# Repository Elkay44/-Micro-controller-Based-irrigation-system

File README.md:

This Arduino sketch is designed for an ESP8266 microcontroller and serves the purpose of monitoring and controlling various sensors, including a DHT11 temperature and humidity sensor, a soil moisture sensor, and a DS18B20 temperature sensor. It communicates with the Blynk platform to facilitate remote sensor data visualization and control. Here's a detailed description of the code:

Libraries and Includes: The code begins by including several libraries, such as Blynk, SimpleTimer, DHT, OneWire, and DallasTemperature. These libraries enable communication with sensors and the Blynk platform.

Variables and Constants: The code defines essential variables and constants, including Blynk authentication, Wi-Fi credentials (SSID and password), pin assignments, sensor thresholds, and relay control pin.

sendSensor() Function: This function is responsible for reading data from the DHT11 sensor, which measures humidity and temperature. It checks for data validity and sends these readings to the Blynk app for remote monitoring. Additionally, it attempts to read data from a soil sensor (though there is a variable 's' used in virtualWrite which is not defined in the code).

setup() Function: This function initializes the ESP8266 device, sets pin modes for various sensors and relay control, and begins serial communication for debugging and communication with the DHT sensor. It configures a timer to periodically call the sendSensor() function for sensor data updates and initializes the DallasTemperature library for the DS18B20 sensor.

sendTemps() Function: This function reads analog data from A0 and requests temperature data from the DS18B20 sensor. It then sends these temperature readings to the Blynk app for remote monitoring.

loop() Function: The main loop function continuously runs and performs the following tasks:

Handles Blynk communication and executes timed functions using the timer.
Calls the sendTemps() function to update temperature readings and sends them to Blynk.
Reads the state of the soil moisture sensor and takes actions based on its state:
If the soil is dry (sensorState is 1 and lastState is 0) and the limit is below 300, it sends a notification to water the plants and turns on the water valve.
If the soil is already wet (sensorState is 1 and lastState is 1), it indicates that the valve is not open.
Otherwise, it turns off the water valve and logs that the valve is closed.
The code effectively integrates multiple sensors, enabling remote monitoring of environmental conditions and plant watering control through the Blynk platform.

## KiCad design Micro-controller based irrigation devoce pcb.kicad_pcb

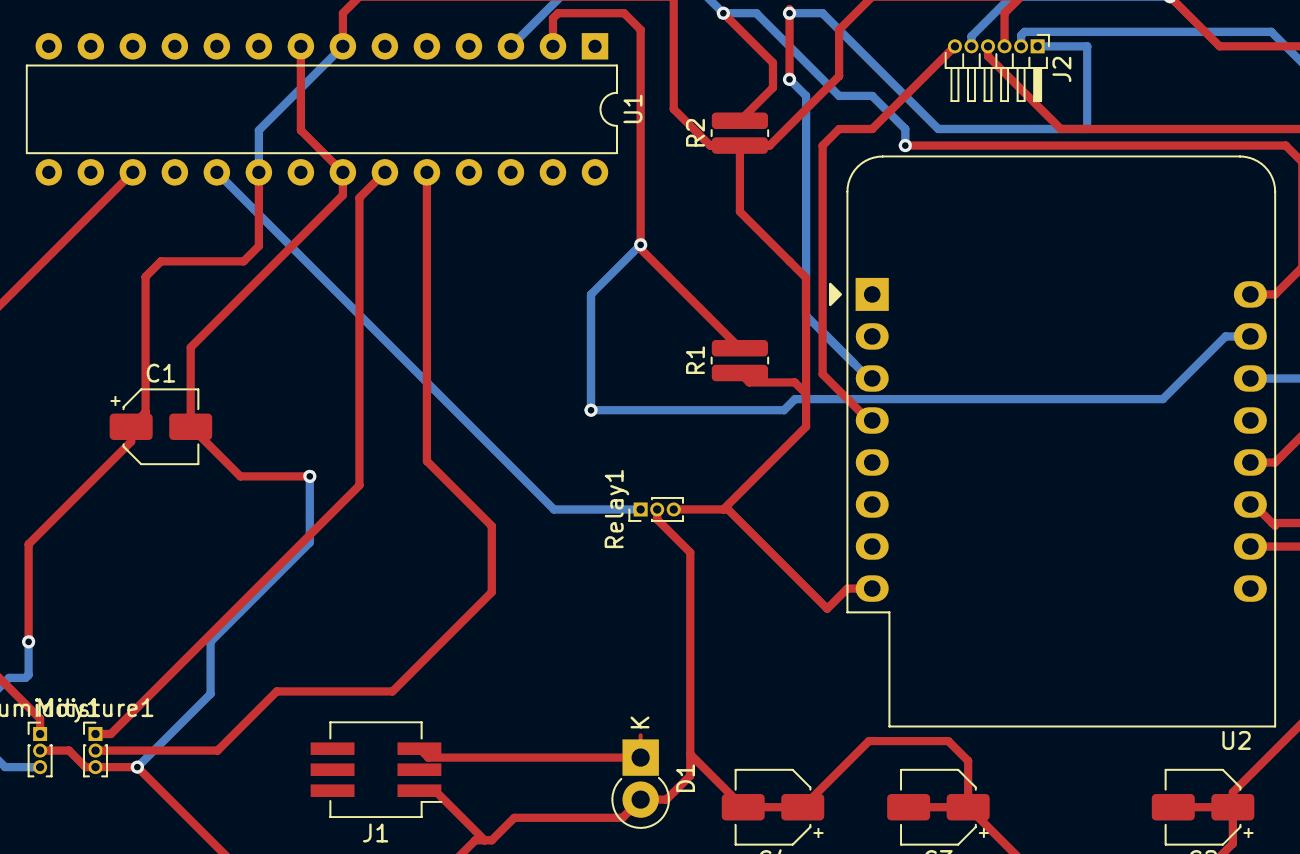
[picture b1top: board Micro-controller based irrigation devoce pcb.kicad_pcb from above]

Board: 2 copper layers, 14 parts (0 on the bottom side), 14 nets.

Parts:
C1: 0.1uF; CP_Elec_4x3.9
C2: 470u; CP_Elec_4x3.9
C3: 470; CP_Elec_4x3.9
C4: 0.1u; CP_Elec_4x3.9
D1: DIODE; D_DO-41_SOD81_P2.54mm_Vertical_KathodeUp
Humidity1: Conn_01x03; PinHeader_1x03_P1.00mm_Vertical
J1: Barrel_Jack_Switch; SW_DIP_SPSTx03_Slide_KingTek_DSHP03TJ_W5.25mm_P1.27mm_JPin
J2: Bluetooth; PinHeader_1x06_P1.00mm_Horizontal
Moisture1: Conn_01x04; PinHeader_1x03_P1.00mm_Vertical
R1, R2: R; R_0612_1632Metric
Relay1: Conn_01x03; PinHeader_1x03_P1.00mm_Vertical
U1: ATmega328P-PU; DIP-28_W7.62mm
U2: WeMos_D1_mini; WEMOS_D1_mini_light

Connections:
+5V: C1.2, C2.1, C2.2, C3.1, C3.2, C4.1, C4.2, D1.2, Humidity1.2, J1.1, Moisture1.3, Relay1.2, U1.8, U1.22, U2.10
unnamed: D1.1, J1.2, J1.3
unnamed: Humidity1.1, U1.17
unnamed: J2.1, U2.3
unnamed: J2.2, U2.14
unnamed: J2.4, U2.12
unnamed: J2.5, U2.11
unnamed: J2.6, U2.4
unnamed: Moisture1.1, U1.23
unnamed: Moisture1.2, U1.24
unnamed: R1.2, U1.2, U2.15
unnamed: R2.2, U1.3, U2.16
unnamed: Relay1.1, U1.19
VCC: C1.1, Humidity1.3, J2.3, R1.1, R2.1, Relay1.3, U1.7, U1.20, U2.8

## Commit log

2023-11-01 README.md
2023-11-01 Code
